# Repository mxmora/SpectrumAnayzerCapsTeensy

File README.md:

# SpectrumAnalyzerCapsTeensy
Spectrum Analyzer board

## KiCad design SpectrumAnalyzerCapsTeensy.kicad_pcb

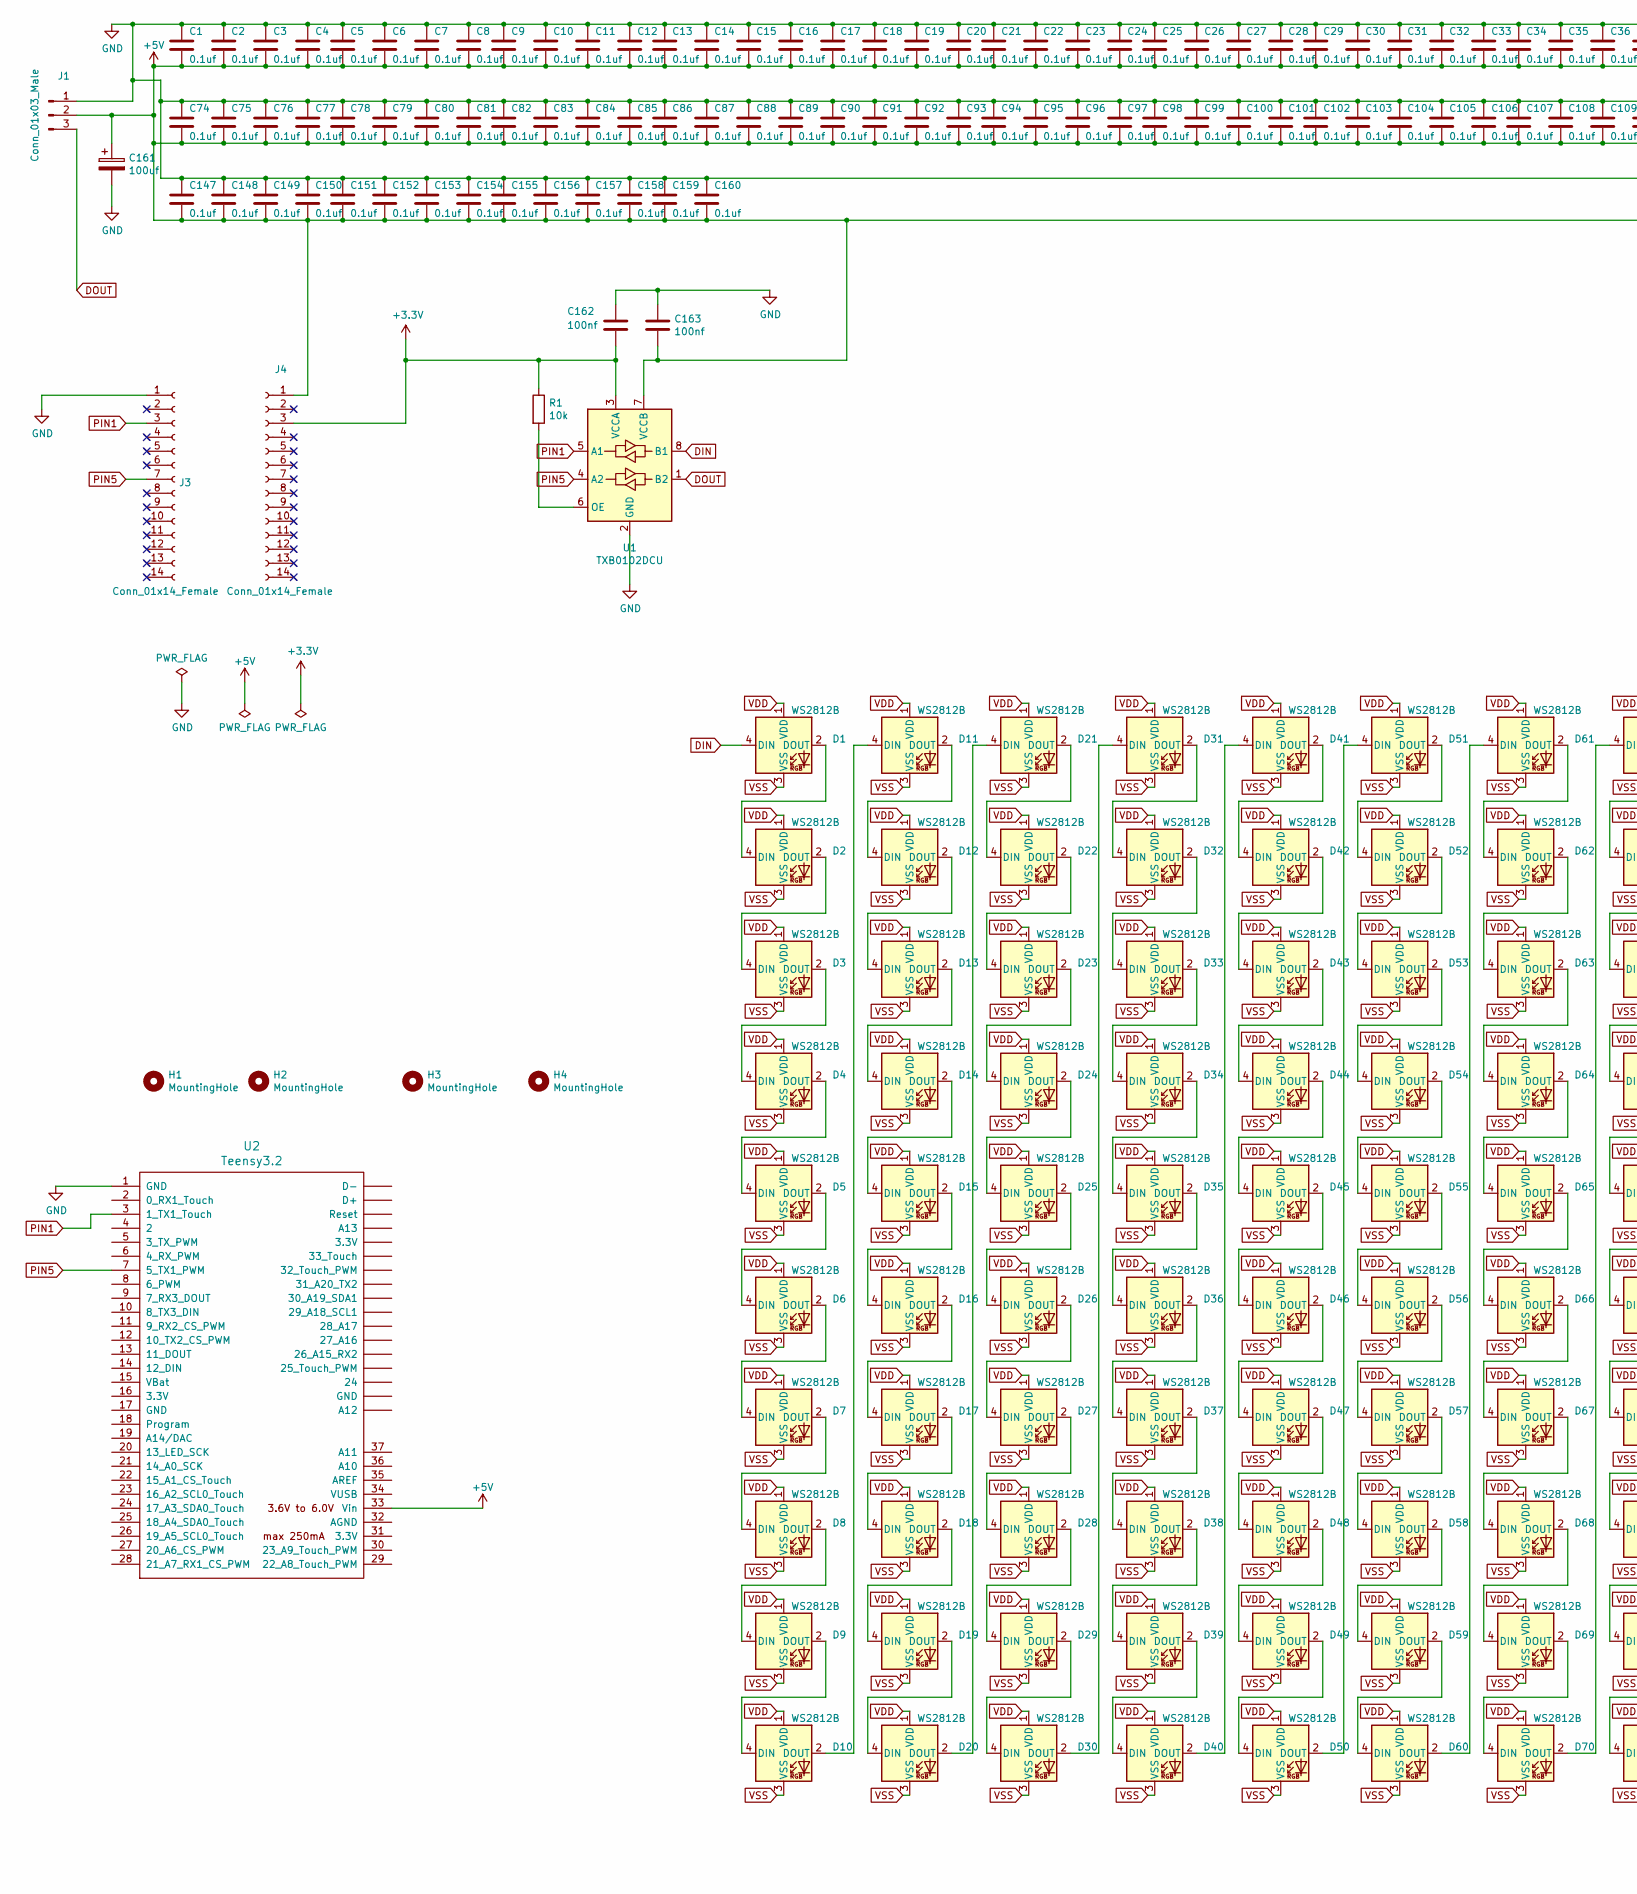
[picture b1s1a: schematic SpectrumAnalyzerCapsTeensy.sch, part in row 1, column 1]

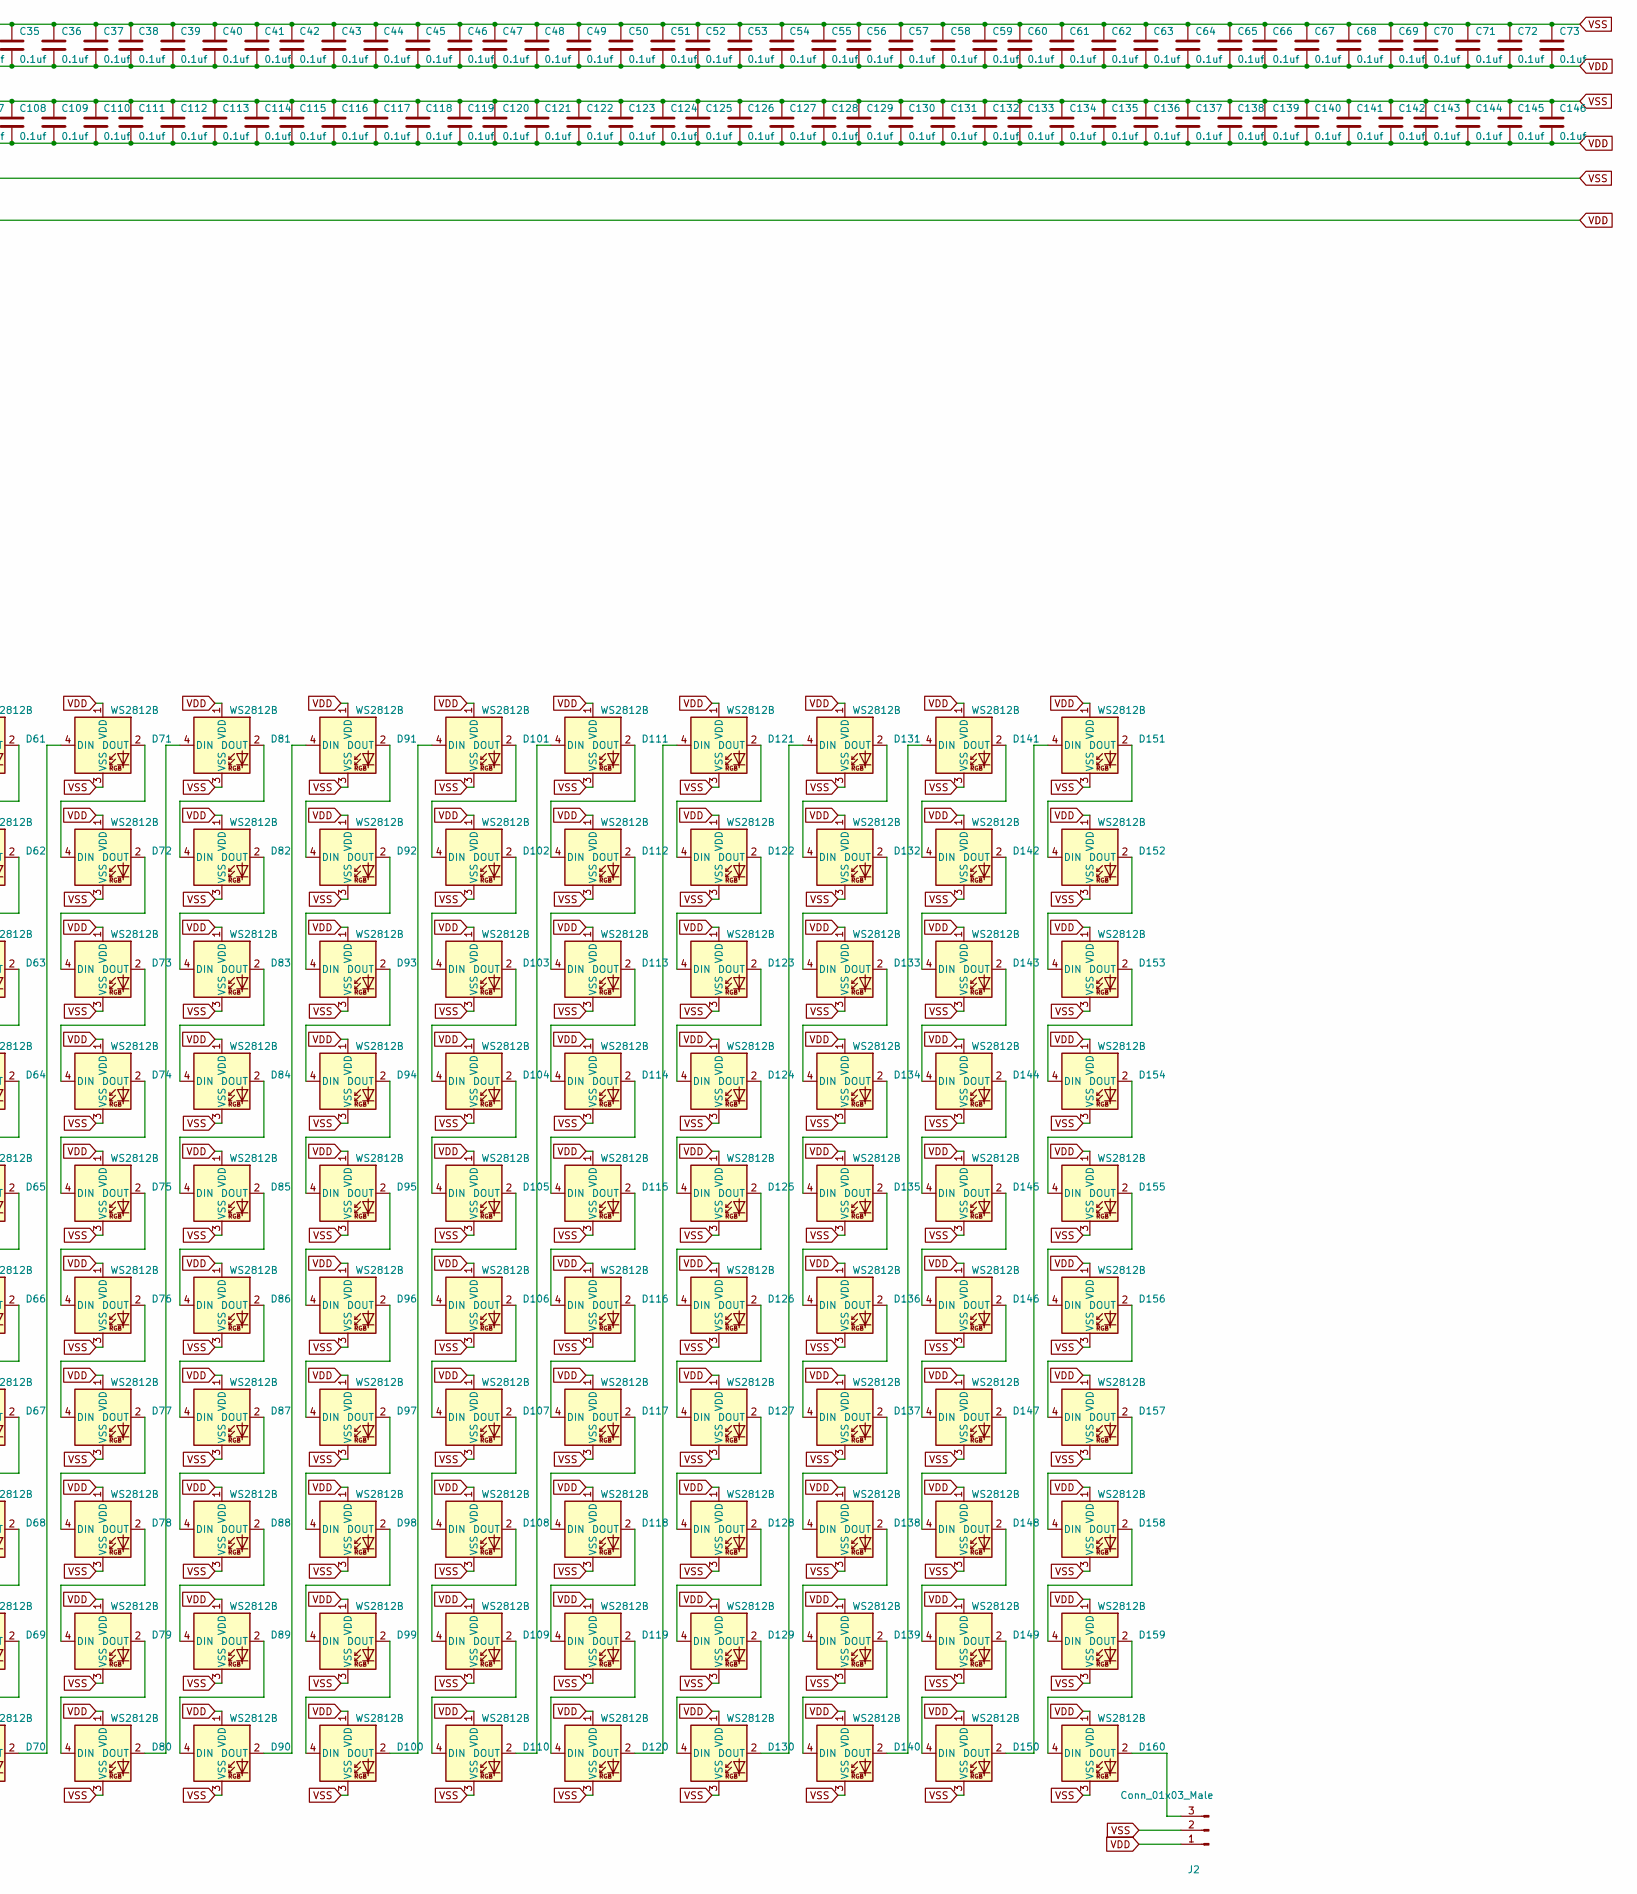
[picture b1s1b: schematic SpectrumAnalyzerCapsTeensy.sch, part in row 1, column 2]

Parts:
C1, C2, C3, C4, C5, C6, C7, C8, C9, C10, C11, C12, C13, C14, C15, C16, C17, C18, C19, C20, C21, C22, C23, C24, C25, C26, C27, C28, C29, C30, C31, C32, C33, C34, C35, C36, C37, C38, C39, C40, C41, C42, C43, C44, C45, C46, C47, C48, C49, C50, C51, C52, C53, C54, C55, C56, C57, C58, C59, C60, C61, C62, C63, C64, C65, C66, C67, C68, C69, C70, C71, C72, C73, C74, C75, C76, C77, C78, C79, C80, C81, C82, C83, C84, C85, C86, C87, C88, C89, C90, C91, C92, C93, C94, C95, C96, C97, C98, C99, C100, C101, C102, C103, C104, C105, C106, C107, C108, C109, C110, C111, C112, C113, C114, C115, C116, C117, C118, C119, C120, C121, C122, C123, C124, C125, C126, C127, C128, C129, C130, C131, C132, C133, C134, C135, C136, C137, C138, C139, C140, C141, C142, C143, C144, C145, C146, C147, C148, C149, C150, C151, C152, C153, C154, C155, C156, C157, C158, C159, C160: 0.1uf; C_0402_1005Metric; LCSC C312124
C161: 100uf; CP_Radial_D5.0mm_P2.50mm
C162, C163: 100nf; C_0402_1005Metric
D1: WS2812B; LED_WS2812B_PLCC4_5.0x5.0mm_P3.2mm; LCSC C114586
D2, D3, D4, D5, D6, D7, D8, D9, D10, D11, D12, D13, D14, D15, D16, D17, D18, D19, D20, D21, D22, D23, D24, D25, D26, D27, D28, D29, D30, D31, D32, D33, D34, D35, D36, D37, D38, D39, D40, D41, D42, D43, D44, D45, D46, D47, D48, D49, D50, D51, D52, D53, D54, D55, D56, D57, D58, D59, D60, D61, D62, D63, D64, D65, D66, D67, D68, D69, D70, D71, D72, D73, D74, D75, D76, D77, D78, D79, D80, D81, D82, D83, D84, D85, D86, D87, D88, D89, D90, D91, D92, D93, D94, D95, D96, D97, D98, D99, D100, D101, D102, D103, D104, D105, D106, D107, D108, D109, D110, D111, D112, D113, D114, D115, D116, D117, D118, D119, D120, D121, D122, D123, D124, D125, D126, D127, D128, D129, D130, D131, D132, D133, D134, D135, D136, D137, D138, D139, D140, D141, D142, D143, D144, D145, D146, D147, D148, D149, D150, D151, D152, D153, D154, D155, D156, D157, D158, D159, D160: WS2812B; LED_WS2812B_PLCC4_5.0x5.0mm_P3.2mm
H1, H2, H3, H4: MountingHole; MountingHole_2.5mm
J1, J2: Conn_01x03_Male; PinHeader_1x03_P2.54mm_Vertical
J3, J4: Conn_01x14_Female; PinSocket_1x14_P2.54mm_Vertical
R1: 10k; R_0402_1005Metric
U1: TXB0102DCU; VSSOP-8_2.4x2.1mm_P0.5mm
U2: Teensy3.2; Teensy30_31_32_LC

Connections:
+3V3: C162.2, J4.3, R1.1, U1.3 (VCCA)
DIN: D1.4 (DIN), U1.8 (B1)
DOUT: J1.3, U1.1 (B2)
unnamed: D1.2 (DOUT), D2.4 (DIN)
unnamed: D2.2 (DOUT), D3.4 (DIN)
unnamed: D3.2 (DOUT), D4.4 (DIN)
unnamed: D4.2 (DOUT), D5.4 (DIN)
unnamed: D5.2 (DOUT), D6.4 (DIN)
unnamed: D6.2 (DOUT), D7.4 (DIN)
unnamed: D7.2 (DOUT), D8.4 (DIN)
unnamed: D8.2 (DOUT), D9.4 (DIN)
unnamed: D10.2 (DOUT), D11.4 (DIN)
unnamed: D9.2 (DOUT), D10.4 (DIN)
unnamed: D11.2 (DOUT), D12.4 (DIN)
unnamed: D12.2 (DOUT), D13.4 (DIN)
unnamed: D13.2 (DOUT), D14.4 (DIN)
unnamed: D14.2 (DOUT), D15.4 (DIN)
unnamed: D15.2 (DOUT), D16.4 (DIN)
unnamed: D16.2 (DOUT), D17.4 (DIN)
unnamed: D17.2 (DOUT), D18.4 (DIN)
unnamed: D18.2 (DOUT), D19.4 (DIN)
unnamed: D19.2 (DOUT), D20.4 (DIN)
unnamed: D20.2 (DOUT), D21.4 (DIN)
unnamed: D21.2 (DOUT), D22.4 (DIN)
unnamed: D22.2 (DOUT), D23.4 (DIN)
unnamed: D23.2 (DOUT), D24.4 (DIN)
unnamed: D24.2 (DOUT), D25.4 (DIN)
unnamed: D25.2 (DOUT), D26.4 (DIN)
unnamed: D26.2 (DOUT), D27.4 (DIN)
unnamed: D27.2 (DOUT), D28.4 (DIN)
unnamed: D28.2 (DOUT), D29.4 (DIN)
unnamed: D29.2 (DOUT), D30.4 (DIN)
unnamed: D30.2 (DOUT), D31.4 (DIN)
unnamed: D31.2 (DOUT), D32.4 (DIN)
unnamed: D32.2 (DOUT), D33.4 (DIN)
unnamed: D33.2 (DOUT), D34.4 (DIN)
unnamed: D34.2 (DOUT), D35.4 (DIN)
unnamed: D35.2 (DOUT), D36.4 (DIN)
unnamed: D36.2 (DOUT), D37.4 (DIN)
unnamed: D37.2 (DOUT), D38.4 (DIN)
unnamed: D38.2 (DOUT), D39.4 (DIN)
unnamed: D39.2 (DOUT), D40.4 (DIN)
unnamed: D40.2 (DOUT), D41.4 (DIN)
unnamed: D41.2 (DOUT), D42.4 (DIN)
unnamed: D42.2 (DOUT), D43.4 (DIN)
unnamed: D43.2 (DOUT), D44.4 (DIN)
unnamed: D44.2 (DOUT), D45.4 (DIN)
unnamed: D45.2 (DOUT), D46.4 (DIN)
unnamed: D46.2 (DOUT), D47.4 (DIN)
unnamed: D47.2 (DOUT), D48.4 (DIN)
unnamed: D48.2 (DOUT), D49.4 (DIN)
unnamed: D49.2 (DOUT), D50.4 (DIN)
unnamed: D50.2 (DOUT), D51.4 (DIN)
unnamed: D51.2 (DOUT), D52.4 (DIN)
unnamed: D52.2 (DOUT), D53.4 (DIN)
unnamed: D53.2 (DOUT), D54.4 (DIN)
unnamed: D54.2 (DOUT), D55.4 (DIN)
unnamed: D55.2 (DOUT), D56.4 (DIN)
unnamed: D56.2 (DOUT), D57.4 (DIN)
unnamed: D57.2 (DOUT), D58.4 (DIN)
unnamed: D58.2 (DOUT), D59.4 (DIN)
unnamed: D59.2 (DOUT), D60.4 (DIN)
unnamed: D60.2 (DOUT), D61.4 (DIN)
unnamed: D61.2 (DOUT), D62.4 (DIN)
unnamed: D62.2 (DOUT), D63.4 (DIN)
unnamed: D63.2 (DOUT), D64.4 (DIN)
unnamed: D64.2 (DOUT), D65.4 (DIN)
unnamed: D65.2 (DOUT), D66.4 (DIN)
unnamed: D66.2 (DOUT), D67.4 (DIN)
unnamed: D67.2 (DOUT), D68.4 (DIN)
unnamed: D68.2 (DOUT), D69.4 (DIN)
unnamed: D69.2 (DOUT), D70.4 (DIN)
unnamed: D70.2 (DOUT), D71.4 (DIN)
unnamed: D71.2 (DOUT), D72.4 (DIN)
unnamed: D72.2 (DOUT), D73.4 (DIN)
unnamed: D73.2 (DOUT), D74.4 (DIN)
unnamed: D74.2 (DOUT), D75.4 (DIN)
unnamed: D75.2 (DOUT), D76.4 (DIN)
unnamed: D76.2 (DOUT), D77.4 (DIN)
unnamed: D77.2 (DOUT), D78.4 (DIN)
unnamed: D78.2 (DOUT), D79.4 (DIN)
unnamed: D79.2 (DOUT), D80.4 (DIN)
unnamed: D80.2 (DOUT), D81.4 (DIN)
unnamed: D81.2 (DOUT), D82.4 (DIN)
unnamed: D82.2 (DOUT), D83.4 (DIN)
unnamed: D83.2 (DOUT), D84.4 (DIN)
unnamed: D84.2 (DOUT), D85.4 (DIN)
unnamed: D85.2 (DOUT), D86.4 (DIN)
unnamed: D86.2 (DOUT), D87.4 (DIN)
unnamed: D87.2 (DOUT), D88.4 (DIN)
unnamed: D88.2 (DOUT), D89.4 (DIN)
unnamed: D89.2 (DOUT), D90.4 (DIN)
unnamed: D90.2 (DOUT), D91.4 (DIN)
unnamed: D91.2 (DOUT), D92.4 (DIN)
unnamed: D92.2 (DOUT), D93.4 (DIN)
unnamed: D93.2 (DOUT), D94.4 (DIN)
unnamed: D94.2 (DOUT), D95.4 (DIN)
unnamed: D95.2 (DOUT), D96.4 (DIN)
unnamed: D96.2 (DOUT), D97.4 (DIN)
unnamed: D97.2 (DOUT), D98.4 (DIN)
unnamed: D98.2 (DOUT), D99.4 (DIN)
unnamed: D100.2 (DOUT), D101.4 (DIN)
unnamed: D99.2 (DOUT), D100.4 (DIN)
unnamed: D101.2 (DOUT), D102.4 (DIN)
unnamed: D102.2 (DOUT), D103.4 (DIN)
unnamed: D103.2 (DOUT), D104.4 (DIN)
unnamed: D104.2 (DOUT), D105.4 (DIN)
unnamed: D105.2 (DOUT), D106.4 (DIN)
unnamed: D106.2 (DOUT), D107.4 (DIN)
unnamed: D107.2 (DOUT), D108.4 (DIN)
unnamed: D108.2 (DOUT), D109.4 (DIN)
unnamed: D109.2 (DOUT), D110.4 (DIN)
unnamed: D110.2 (DOUT), D111.4 (DIN)
unnamed: D111.2 (DOUT), D112.4 (DIN)
unnamed: D112.2 (DOUT), D113.4 (DIN)
unnamed: D113.2 (DOUT), D114.4 (DIN)
unnamed: D114.2 (DOUT), D115.4 (DIN)
unnamed: D115.2 (DOUT), D116.4 (DIN)
unnamed: D116.2 (DOUT), D117.4 (DIN)
unnamed: D117.2 (DOUT), D118.4 (DIN)
unnamed: D118.2 (DOUT), D119.4 (DIN)
unnamed: D119.2 (DOUT), D120.4 (DIN)
unnamed: D120.2 (DOUT), D121.4 (DIN)
unnamed: D121.2 (DOUT), D122.4 (DIN)
unnamed: D122.2 (DOUT), D123.4 (DIN)
unnamed: D123.2 (DOUT), D124.4 (DIN)
unnamed: D124.2 (DOUT), D125.4 (DIN)
unnamed: D125.2 (DOUT), D126.4 (DIN)
unnamed: D126.2 (DOUT), D127.4 (DIN)
unnamed: D127.2 (DOUT), D128.4 (DIN)
unnamed: D128.2 (DOUT), D129.4 (DIN)
unnamed: D129.2 (DOUT), D130.4 (DIN)
unnamed: D130.2 (DOUT), D131.4 (DIN)
unnamed: D131.2 (DOUT), D132.4 (DIN)
unnamed: D132.2 (DOUT), D133.4 (DIN)
unnamed: D133.2 (DOUT), D134.4 (DIN)
unnamed: D134.2 (DOUT), D135.4 (DIN)
unnamed: D135.2 (DOUT), D136.4 (DIN)
unnamed: D136.2 (DOUT), D137.4 (DIN)
unnamed: D137.2 (DOUT), D138.4 (DIN)
unnamed: D138.2 (DOUT), D139.4 (DIN)
unnamed: D139.2 (DOUT), D140.4 (DIN)
unnamed: D140.2 (DOUT), D141.4 (DIN)
unnamed: D141.2 (DOUT), D142.4 (DIN)
unnamed: D142.2 (DOUT), D143.4 (DIN)
unnamed: D143.2 (DOUT), D144.4 (DIN)
unnamed: D144.2 (DOUT), D145.4 (DIN)
unnamed: D145.2 (DOUT), D146.4 (DIN)
unnamed: D146.2 (DOUT), D147.4 (DIN)
unnamed: D147.2 (DOUT), D148.4 (DIN)
unnamed: D148.2 (DOUT), D149.4 (DIN)
unnamed: D149.2 (DOUT), D150.4 (DIN)
unnamed: D150.2 (DOUT), D151.4 (DIN)
unnamed: D151.2 (DOUT), D152.4 (DIN)
unnamed: D152.2 (DOUT), D153.4 (DIN)
unnamed: D153.2 (DOUT), D154.4 (DIN)
unnamed: D154.2 (DOUT), D155.4 (DIN)
unnamed: D155.2 (DOUT), D156.4 (DIN)
unnamed: D156.2 (DOUT), D157.4 (DIN)
unnamed: D157.2 (DOUT), D158.4 (DIN)
unnamed: D158.2 (DOUT), D159.4 (DIN)
unnamed: D159.2 (DOUT), D160.4 (DIN)
unnamed: D160.2 (DOUT), J2.3
unnamed: R1.2, U1.6 (OE)
PIN1: J3.3, U1.5 (A1), U2.3 (1_TX1_Touch)
PIN5: J3.7, U1.4 (A2), U2.7 (5_TX1_PWM)
VDD: C1.2, C2.2, C3.2, C4.2, C5.2, C6.2, C7.2, C8.2, C9.2, C10.2, C11.2, C12.2, C13.2, C14.2, C15.2, C16.2, C17.2, C18.2, C19.2, C20.2, C21.2, C22.2, C23.2, C24.2, C25.2, C26.2, C27.2, C28.2, C29.2, C30.2, C31.2, C32.2, C33.2, C34.2, C35.2, C36.2, C37.2, C38.2, C39.2, C40.2, C41.2, C42.2, C43.2, C44.2, C45.2, C46.2, C47.2, C48.2, C49.2, C50.2, C51.2, C52.2, C53.2, C54.2, C55.2, C56.2, C57.2, C58.2, C59.2, C60.2, C61.2, C62.2, C63.2, C64.2, C65.2, C66.2, C67.2, C68.2, C69.2, C70.2, C71.2, C72.2, C73.2, C74.2, C75.2, C76.2, C77.2, C78.2, C79.2, C80.2, C81.2, C82.2, C83.2, C84.2, C85.2, C86.2, C87.2, C88.2, C89.2, C90.2, C91.2, C92.2, C93.2, C94.2, C95.2, C96.2, C97.2, C98.2, C99.2, C100.2, C101.2, C102.2, C103.2, C104.2, C105.2, C106.2, C107.2, C108.2, C109.2, C110.2, C111.2, C112.2, C113.2, C114.2, C115.2, C116.2, C117.2, C118.2, C119.2, C120.2, C121.2, C122.2, C123.2, C124.2, C125.2, C126.2, C127.2, C128.2, C129.2, C130.2, C131.2, C132.2, C133.2, C134.2, C135.2, C136.2, C137.2, C138.2, C139.2, C140.2, C141.2, C142.2, C143.2, C144.2, C145.2, C146.2, C147.2, C148.2, C149.2, C150.2, C151.2, C152.2, C153.2, C154.2, C155.2, C156.2, C157.2, C158.2, C159.2, C160.2, C161.1, C163.2, D1.1 (VDD), D2.1 (VDD), D3.1 (VDD), D4.1 (VDD), D5.1 (VDD), D6.1 (VDD), D7.1 (VDD), D8.1 (VDD), D9.1 (VDD), D10.1 (VDD), D11.1 (VDD), D12.1 (VDD), D13.1 (VDD), D14.1 (VDD), D15.1 (VDD), D16.1 (VDD), D17.1 (VDD), D18.1 (VDD), D19.1 (VDD), D20.1 (VDD), D21.1 (VDD), D22.1 (VDD), D23.1 (VDD), D24.1 (VDD), D25.1 (VDD), D26.1 (VDD), D27.1 (VDD), D28.1 (VDD), D29.1 (VDD), D30.1 (VDD), D31.1 (VDD), D32.1 (VDD), D33.1 (VDD), D34.1 (VDD), D35.1 (VDD), D36.1 (VDD), D37.1 (VDD), D38.1 (VDD), D39.1 (VDD), D40.1 (VDD), D41.1 (VDD), D42.1 (VDD), D43.1 (VDD), D44.1 (VDD), D45.1 (VDD), D46.1 (VDD), D47.1 (VDD), D48.1 (VDD), D49.1 (VDD), D50.1 (VDD), D51.1 (VDD), D52.1 (VDD), D53.1 (VDD), D54.1 (VDD), D55.1 (VDD), D56.1 (VDD), D57.1 (VDD), D58.1 (VDD), D59.1 (VDD), D60.1 (VDD), D61.1 (VDD), D62.1 (VDD), D63.1 (VDD), D64.1 (VDD), D65.1 (VDD), D66.1 (VDD), D67.1 (VDD), D68.1 (VDD), D69.1 (VDD), D70.1 (VDD), D71.1 (VDD), D72.1 (VDD), D73.1 (VDD), D74.1 (VDD), D75.1 (VDD), D76.1 (VDD), D77.1 (VDD), D78.1 (VDD), D79.1 (VDD), D80.1 (VDD), D81.1 (VDD), D82.1 (VDD), D83.1 (VDD), D84.1 (VDD), D85.1 (VDD), D86.1 (VDD), D87.1 (VDD), D88.1 (VDD), D89.1 (VDD), D90.1 (VDD), D91.1 (VDD), D92.1 (VDD), D93.1 (VDD), D94.1 (VDD), D95.1 (VDD), D96.1 (VDD), D97.1 (VDD), D98.1 (VDD), D99.1 (VDD), D100.1 (VDD), D101.1 (VDD), D102.1 (VDD), D103.1 (VDD), D104.1 (VDD), D105.1 (VDD), D106.1 (VDD), D107.1 (VDD), D108.1 (VDD), D109.1 (VDD), D110.1 (VDD), D111.1 (VDD), D112.1 (VDD), D113.1 (VDD), D114.1 (VDD), D115.1 (VDD), D116.1 (VDD), D117.1 (VDD), D118.1 (VDD), D119.1 (VDD), D120.1 (VDD), D121.1 (VDD), D122.1 (VDD), D123.1 (VDD), D124.1 (VDD), D125.1 (VDD), D126.1 (VDD), D127.1 (VDD), D128.1 (VDD), D129.1 (VDD), D130.1 (VDD), D131.1 (VDD), D132.1 (VDD), D133.1 (VDD), D134.1 (VDD), D135.1 (VDD), D136.1 (VDD), D137.1 (VDD), D138.1 (VDD), D139.1 (VDD), D140.1 (VDD), D141.1 (VDD), D142.1 (VDD), D143.1 (VDD), D144.1 (VDD), D145.1 (VDD), D146.1 (VDD), D147.1 (VDD), D148.1 (VDD), D149.1 (VDD), D150.1 (VDD), D151.1 (VDD), D152.1 (VDD), D153.1 (VDD), D154.1 (VDD), D155.1 (VDD), D156.1 (VDD), D157.1 (VDD), D158.1 (VDD), D159.1 (VDD), D160.1 (VDD), J1.2, J2.1, J4.1, U1.7 (VCCB), U2.33 (Vin)
VSS: C1.1, C2.1, C3.1, C4.1, C5.1, C6.1, C7.1, C8.1, C9.1, C10.1, C11.1, C12.1, C13.1, C14.1, C15.1, C16.1, C17.1, C18.1, C19.1, C20.1, C21.1, C22.1, C23.1, C24.1, C25.1, C26.1, C27.1, C28.1, C29.1, C30.1, C31.1, C32.1, C33.1, C34.1, C35.1, C36.1, C37.1, C38.1, C39.1, C40.1, C41.1, C42.1, C43.1, C44.1, C45.1, C46.1, C47.1, C48.1, C49.1, C50.1, C51.1, C52.1, C53.1, C54.1, C55.1, C56.1, C57.1, C58.1, C59.1, C60.1, C61.1, C62.1, C63.1, C64.1, C65.1, C66.1, C67.1, C68.1, C69.1, C70.1, C71.1, C72.1, C73.1, C74.1, C75.1, C76.1, C77.1, C78.1, C79.1, C80.1, C81.1, C82.1, C83.1, C84.1, C85.1, C86.1, C87.1, C88.1, C89.1, C90.1, C91.1, C92.1, C93.1, C94.1, C95.1, C96.1, C97.1, C98.1, C99.1, C100.1, C101.1, C102.1, C103.1, C104.1, C105.1, C106.1, C107.1, C108.1, C109.1, C110.1, C111.1, C112.1, C113.1, C114.1, C115.1, C116.1, C117.1, C118.1, C119.1, C120.1, C121.1, C122.1, C123.1, C124.1, C125.1, C126.1, C127.1, C128.1, C129.1, C130.1, C131.1, C132.1, C133.1, C134.1, C135.1, C136.1, C137.1, C138.1, C139.1, C140.1, C141.1, C142.1, C143.1, C144.1, C145.1, C146.1, C147.1, C148.1, C149.1, C150.1, C151.1, C152.1, C153.1, C154.1, C155.1, C156.1, C157.1, C158.1, C159.1, C160.1, C161.2, C162.1, C163.1, D1.3 (VSS), D2.3 (VSS), D3.3 (VSS), D4.3 (VSS), D5.3 (VSS), D6.3 (VSS), D7.3 (VSS), D8.3 (VSS), D9.3 (VSS), D10.3 (VSS), D11.3 (VSS), D12.3 (VSS), D13.3 (VSS), D14.3 (VSS), D15.3 (VSS), D16.3 (VSS), D17.3 (VSS), D18.3 (VSS), D19.3 (VSS), D20.3 (VSS), D21.3 (VSS), D22.3 (VSS), D23.3 (VSS), D24.3 (VSS), D25.3 (VSS), D26.3 (VSS), D27.3 (VSS), D28.3 (VSS), D29.3 (VSS), D30.3 (VSS), D31.3 (VSS), D32.3 (VSS), D33.3 (VSS), D34.3 (VSS), D35.3 (VSS), D36.3 (VSS), D37.3 (VSS), D38.3 (VSS), D39.3 (VSS), D40.3 (VSS), D41.3 (VSS), D42.3 (VSS), D43.3 (VSS), D44.3 (VSS), D45.3 (VSS), D46.3 (VSS), D47.3 (VSS), D48.3 (VSS), D49.3 (VSS), D50.3 (VSS), D51.3 (VSS), D52.3 (VSS), D53.3 (VSS), D54.3 (VSS), D55.3 (VSS), D56.3 (VSS), D57.3 (VSS), D58.3 (VSS), D59.3 (VSS), D60.3 (VSS), D61.3 (VSS), D62.3 (VSS), D63.3 (VSS), D64.3 (VSS), D65.3 (VSS), D66.3 (VSS), D67.3 (VSS), D68.3 (VSS), D69.3 (VSS), D70.3 (VSS), D71.3 (VSS), D72.3 (VSS), D73.3 (VSS), D74.3 (VSS), D75.3 (VSS), D76.3 (VSS), D77.3 (VSS), D78.3 (VSS), D79.3 (VSS), D80.3 (VSS), D81.3 (VSS), D82.3 (VSS), D83.3 (VSS), D84.3 (VSS), D85.3 (VSS), D86.3 (VSS), D87.3 (VSS), D88.3 (VSS), D89.3 (VSS), D90.3 (VSS), D91.3 (VSS), D92.3 (VSS), D93.3 (VSS), D94.3 (VSS), D95.3 (VSS), D96.3 (VSS), D97.3 (VSS), D98.3 (VSS), D99.3 (VSS), D100.3 (VSS), D101.3 (VSS), D102.3 (VSS), D103.3 (VSS), D104.3 (VSS), D105.3 (VSS), D106.3 (VSS), D107.3 (VSS), D108.3 (VSS), D109.3 (VSS), D110.3 (VSS), D111.3 (VSS), D112.3 (VSS), D113.3 (VSS), D114.3 (VSS), D115.3 (VSS), D116.3 (VSS), D117.3 (VSS), D118.3 (VSS), D119.3 (VSS), D120.3 (VSS), D121.3 (VSS), D122.3 (VSS), D123.3 (VSS), D124.3 (VSS), D125.3 (VSS), D126.3 (VSS), D127.3 (VSS), D128.3 (VSS), D129.3 (VSS), D130.3 (VSS), D131.3 (VSS), D132.3 (VSS), D133.3 (VSS), D134.3 (VSS), D135.3 (VSS), D136.3 (VSS), D137.3 (VSS), D138.3 (VSS), D139.3 (VSS), D140.3 (VSS), D141.3 (VSS), D142.3 (VSS), D143.3 (VSS), D144.3 (VSS), D145.3 (VSS), D146.3 (VSS), D147.3 (VSS), D148.3 (VSS), D149.3 (VSS), D150.3 (VSS), D151.3 (VSS), D152.3 (VSS), D153.3 (VSS), D154.3 (VSS), D155.3 (VSS), D156.3 (VSS), D157.3 (VSS), D158.3 (VSS), D159.3 (VSS), D160.3 (VSS), J1.1, J2.2, J3.1, U1.2 (GND), U2.1 (GND)

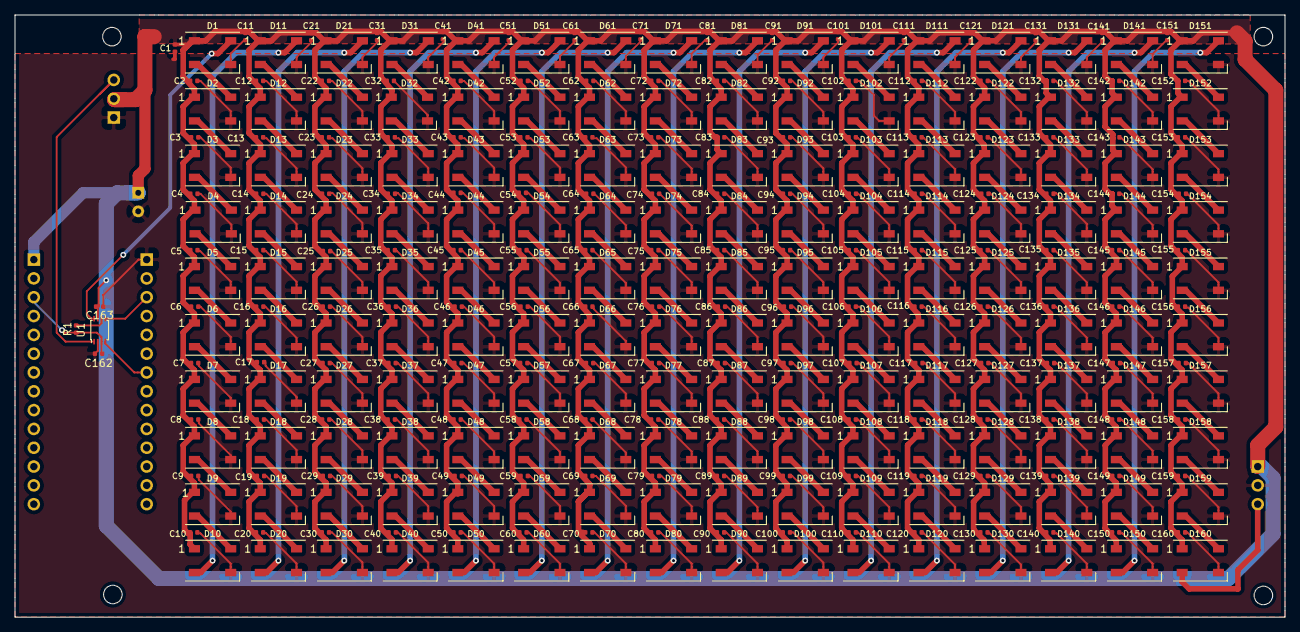
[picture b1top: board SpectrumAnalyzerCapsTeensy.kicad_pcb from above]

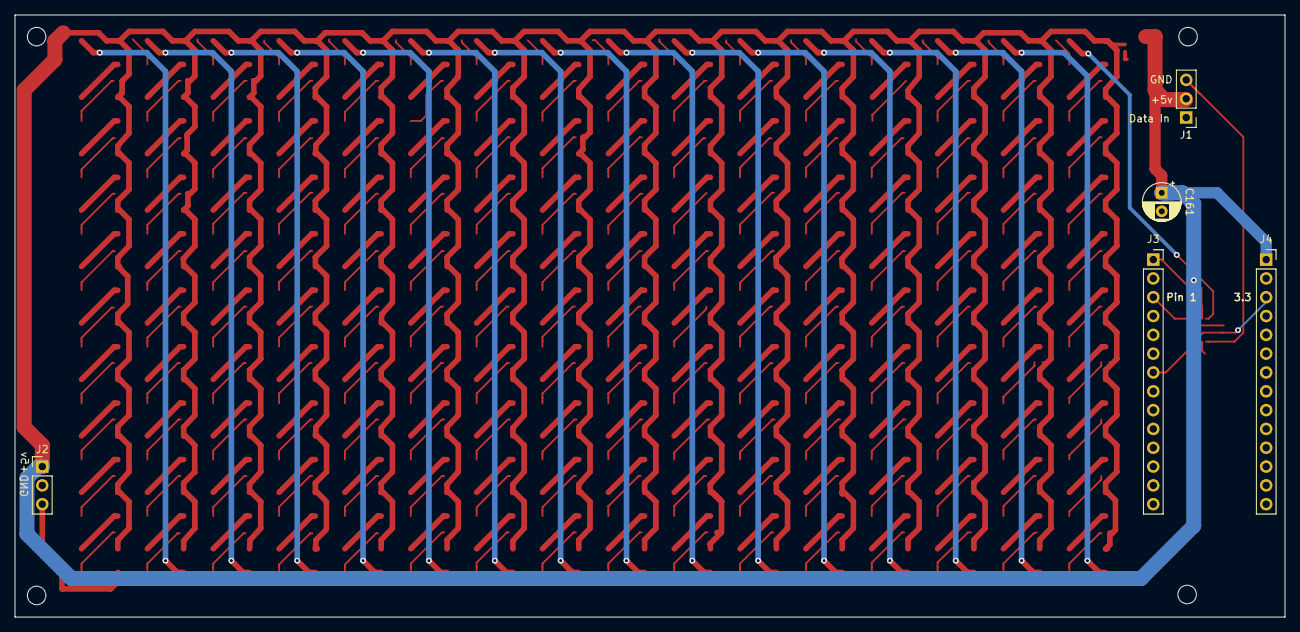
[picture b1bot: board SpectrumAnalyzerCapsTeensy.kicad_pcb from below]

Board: 2 copper layers, 171.5 x 81.3 mm, 333 parts (5 on the bottom side), 168 nets.

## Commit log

2020-02-09 first check in
